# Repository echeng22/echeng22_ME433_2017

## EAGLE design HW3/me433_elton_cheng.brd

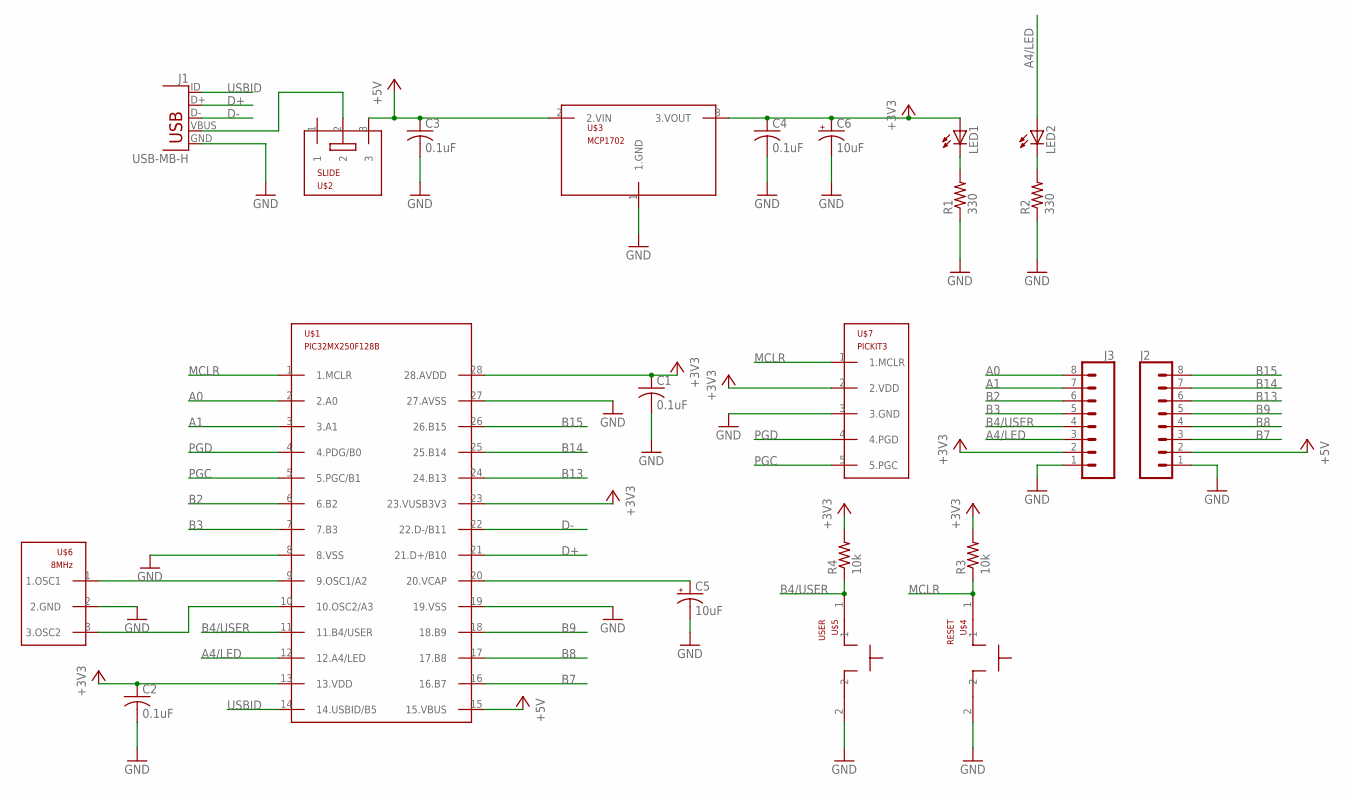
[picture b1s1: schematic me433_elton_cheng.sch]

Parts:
C1, C2, C3, C4: 0.1uF; C025-025X050
C5, C6: 10uF; B45181B
J1: USB-MB-H
J2, J3: CONN_08; 1X08
LED1, LED2: LED3MM
R1, R2: 330; 0207/10
R3, R4: 10k; 0207/10
U$1: PIC32MX250F128B; DIL28-3
U$2: SLIDE
U$3: MCP1702; TO92
U$4: RESET; PB
U$5: USER; PB
U$6: 8MHz; OSC
U$7: PICKIT3; 1X05

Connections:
+3V3: C1.1, C2.1, C4.1, C6.+, J3.2, LED1.A, R3.2, R4.2, U$1.13 (13.VDD), U$1.28 (28.AVDD), U$3.3 (3.VOUT), U$7.2 (2.VDD)
+5V: C3.1, J2.2, U$1.15 (15.VBUS), U$2.3, U$3.2 (2.VIN)
A0: J3.8, U$1.2 (2.A0)
A1: J3.7, U$1.3 (3.A1)
A4/LED: J3.3, LED2.A, U$1.12 (12.A4/LED)
B2: J3.6, U$1.6 (6.B2)
B3: J3.5, U$1.7 (7.B3)
B4/USER: J3.4, R4.1, U$1.11 (11.B4/USER), U$5.1
B7: J2.3, U$1.16 (16.B7)
B8: J2.4, U$1.17 (17.B8)
B9: J2.5, U$1.18 (18.B9)
B13: J2.6, U$1.24 (24.B13)
B14: J2.7, U$1.25 (25.B14)
B15: J2.8, U$1.26 (26.B15)
D+: J1.D+, U$1.21 (21.D+/B10)
D-: J1.D-, U$1.22 (22.D-/B11)
GND: C1.2, C2.2, C3.2, C4.2, C5.-, C6.-, J1.GND, J2.1, J3.1, R1.1, R2.1, U$1.8 (8.VSS), U$1.19 (19.VSS), U$1.27 (27.AVSS), U$3.1 (1.GND), U$4.2, U$5.2, U$6.2 (2.GND), U$7.3 (3.GND)
MCLR: R3.1, U$1.1 (1.MCLR), U$4.1, U$7.1 (1.MCLR)
unnamed: LED1.K (C), R1.2
unnamed: C5.+, U$1.20 (20.VCAP)
unnamed: LED2.K (C), R2.2
unnamed: U$1.9 (9.OSC1/A2), U$6.1 (1.OSC1)
unnamed: U$1.10 (10.OSC2/A3), U$6.3 (3.OSC2)
PGC: U$1.5 (5.PGC/B1), U$7.5 (5.PGC)
PGD: U$1.4 (4.PDG/B0), U$7.4 (4.PGD)
USBID: J1.ID, U$1.14 (14.USBID/B5)
VBUS: J1.VBUS, U$2.2

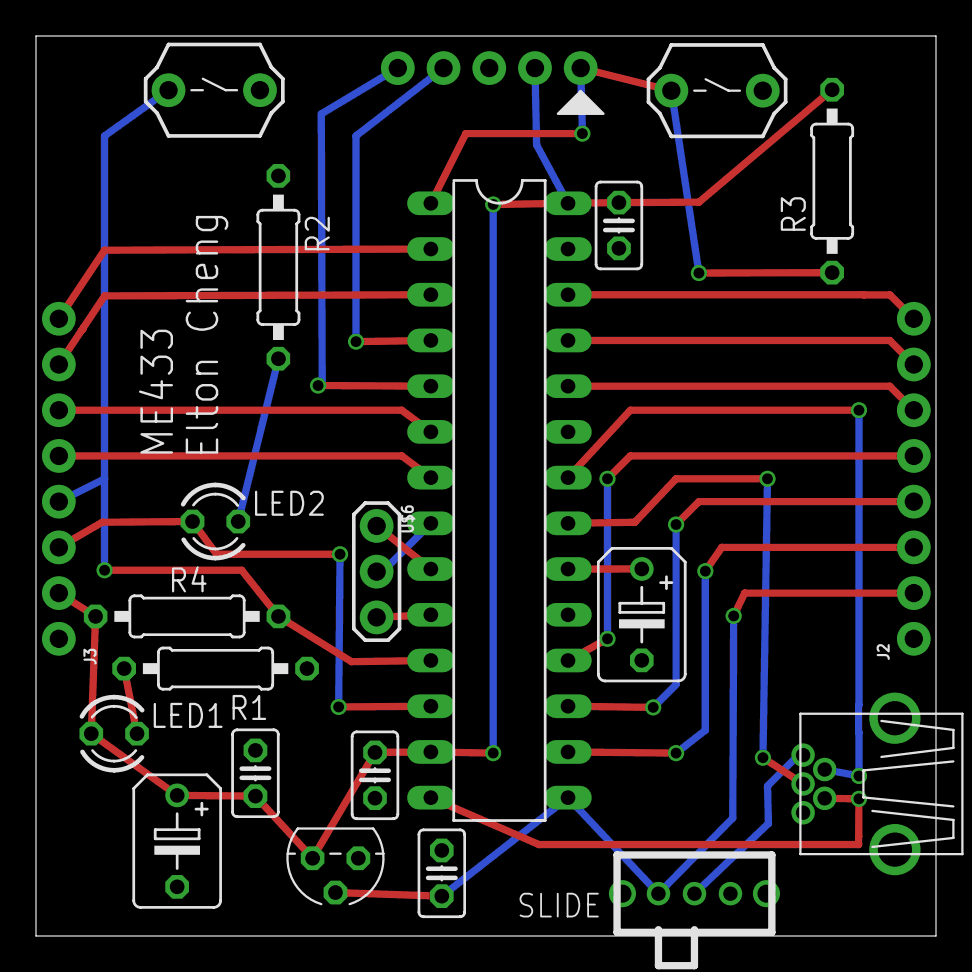
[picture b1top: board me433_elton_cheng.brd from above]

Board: 2 copper layers, 50.0 x 50.0 mm, 22 parts (1 on the bottom side), 27 nets.

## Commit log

2017-03-28 Created Repo. Added main.c into hw1 folder
2017-03-28 Added template code
2017-03-28 Added some variables definitions.
2017-03-29 Added pictures of clean and oscillating signal
2017-03-29 Finished code. Will test to make sure it goes at 1kHz.
2017-03-29 Found timing to get .05 ms wave. Done
2017-03-29 Added breadboard and circuit diagram deliverables.
2017-04-03 Finished making library. Working on schematic now.
2017-04-04 Finished schematic. Working on board design
2017-04-05 Adding bmp image for pcb.
2017-04-06 Board design finished. Gerber files created.
2017-04-07 Added board
2017-04-11 HW4 code
2017-04-11 Finished code for hw4. Will upload pictures
2017-04-11 Adjusted frequency of signals. Added picture. Uploaded picture. Completed.
2017-04-11 Added schematic drawing
2017-04-20 Start on HW5
2017-04-21 Working code for hw5. Working on circuit diagram and video
2017-04-21 Added picture of circuit. Homework completed.
2017-04-21 Started on HW6. Working on getting code for writing to lcd working.
2017-04-22 Working character and string printing to LCD code. Working on progress bar printing.
2017-04-22 Finished draing bar code. Works with FPS stuff.
2017-04-24 Fixed FPS counter. Code is finished.
2017-04-25 Finished hw7 code
2017-04-26 Finished HW8. Code is all done
2017-04-26 Started HW9
2017-04-27 Forgot to add in hw7 main
2017-04-27 HW9 stuff before restarting MPLAB
2017-04-27 HW9 stuff
2017-04-27 Updated some code
2017-04-27 Finished hw9
2017-05-05 Updated HW10 code. Mostly completed
2017-05-06 Updated code, fixed small bug on python code. Should be done
2017-05-06 Hw11 started
2017-05-06 Finished HW11
2017-05-12 Finished HW12
2017-05-12 Created HW13 and HW13_2. HW13 is set up with opencv. HW13_2 is with the shortcut method
2017-05-12 Added gitignore to ignore opencv libraries
2017-05-12 Removed open cv library from git cache
2017-05-12 Added HW13_2 folder
2017-05-13 HW13 completed. Works for a larger bitmap, so that it looks better on my larger phone
2017-05-18 Finished HW14
2017-05-27 Added box designs/dxf files.
2017-05-27 Uploaded pictures of 3d printed wheel
2017-05-29 Added pictures for laser cut parts assembled.
2017-06-06 Finished motor control for HW19
2017-06-06 Updated code to include servo control
2017-06-06 Named HW18 as HW19. Updated files to be put in HW18 folder
2017-06-07 Finished HW19 code without opencv
2017-06-08 Added code for HW20. Updated some files in other folders
2017-06-08 Finished changing control algorithm on android app. Using HW 18 Motor control code for the PIC
